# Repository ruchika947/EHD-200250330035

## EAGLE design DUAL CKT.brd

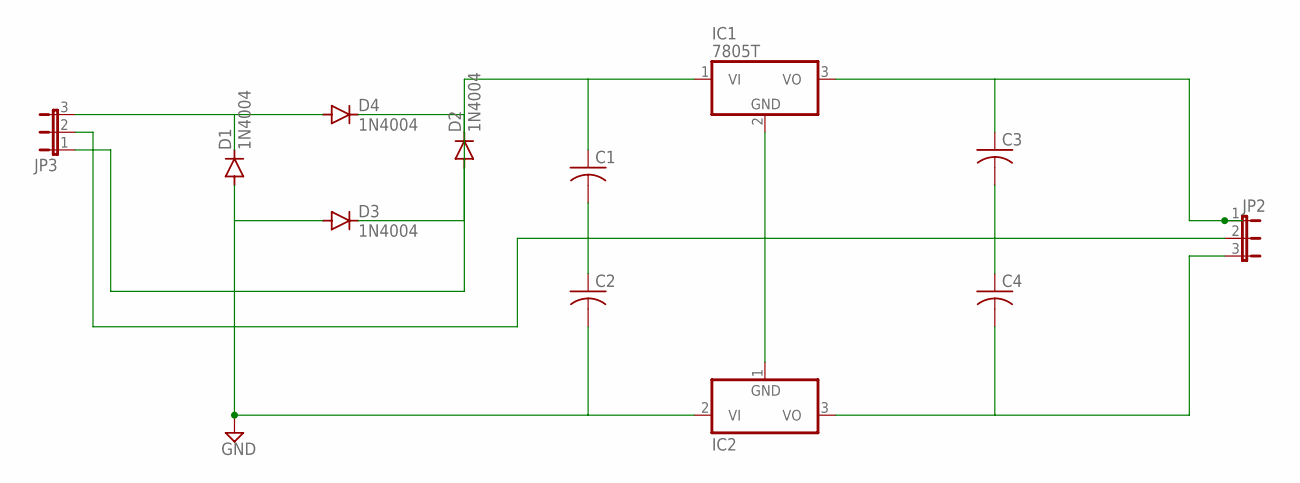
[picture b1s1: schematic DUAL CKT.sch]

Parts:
C1, C2, C3, C4: C-US025-024X044; C025-024X044
D1, D2, D3, D4: 1N4004; DO41-10
IC1: 7805T; TO220H
IC2: 7905T; TO220H
JP2, JP3: JP2W

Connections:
GND: C2.2, D1.A, D3.A, IC2.2 (VI)
unnamed: D1.C, D4.A, JP3.3
unnamed: C1.1, D2.C, D4.C, IC1.1 (VI), JP3.1
unnamed: JP2.2, JP3.2
unnamed: C1.2, C2.1
unnamed: C3.1, IC1.3 (VO), JP2.1
unnamed: C4.2, IC2.3 (VO), JP2.3
unnamed: IC1.2 (GND), IC2.1 (GND)
unnamed: C3.2, C4.1
unnamed: D2.A, D3.C

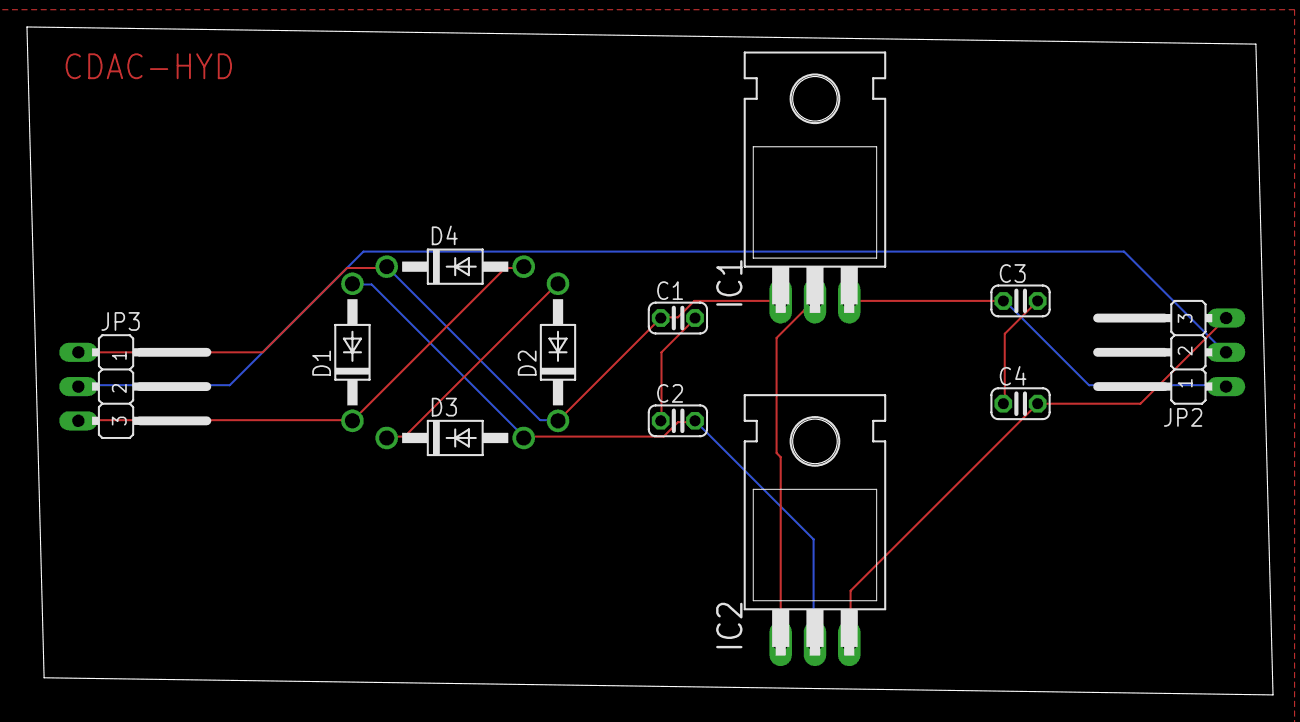
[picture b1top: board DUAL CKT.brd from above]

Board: 2 copper layers, 92.4 x 49.5 mm, 12 parts (0 on the bottom side), 10 nets.

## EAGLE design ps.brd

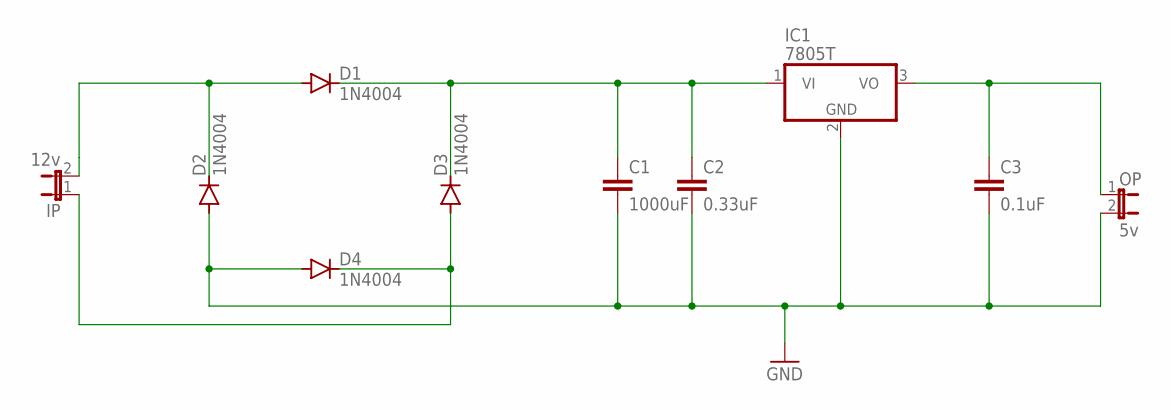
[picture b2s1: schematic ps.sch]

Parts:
C1: 1000uF; C2.5-3
C2: 0.33uF; C2.5-3
C3: 0.1uF; C2.5-3
D1, D2, D3, D4: 1N4004; DO41-10
IC1: 7805T; TO220H
IP: 12v; JP1
OP: 5v; JP1

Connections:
GND: C1.2, C2.2, C3.2, D2.A, D4.A, IC1.2 (GND), OP.2
unnamed: D1.A, D2.C, IP.2
unnamed: C1.1, C2.1, D1.C, D3.C, IC1.1 (VI)
unnamed: D3.A, D4.C, IP.1
unnamed: C3.1, IC1.3 (VO), OP.1

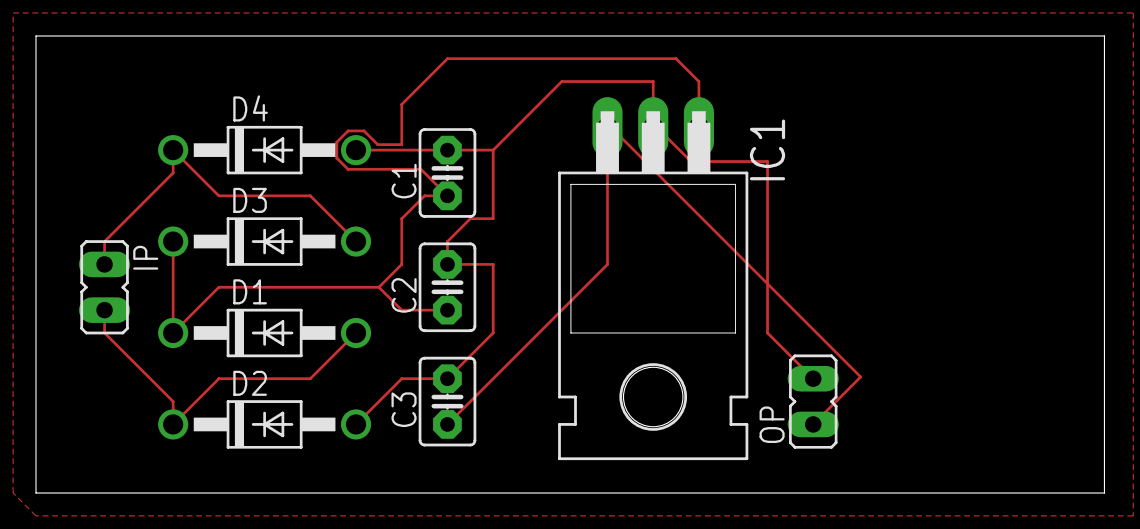
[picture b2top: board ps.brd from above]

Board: 2 copper layers, 59.4 x 25.4 mm, 10 parts (0 on the bottom side), 5 nets.

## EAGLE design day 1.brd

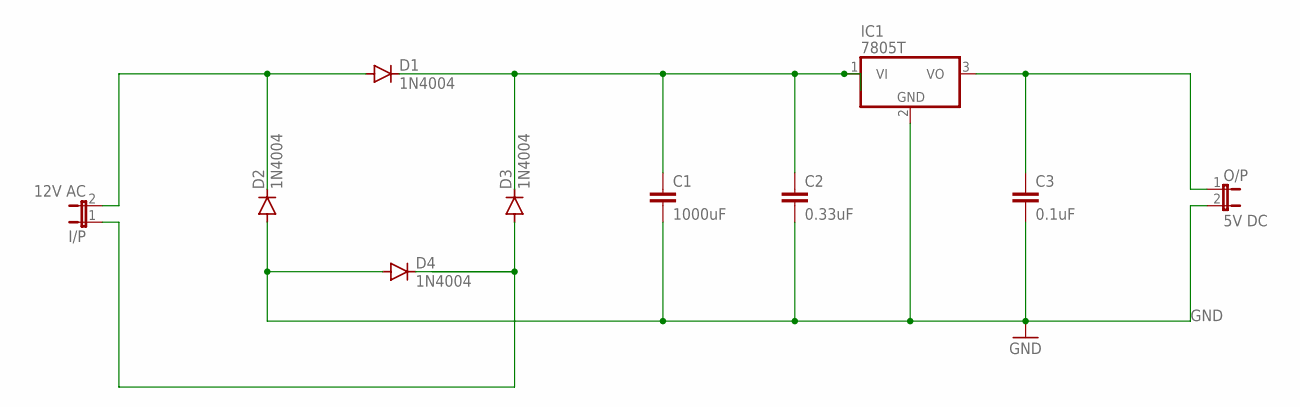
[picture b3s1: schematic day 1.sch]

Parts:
C1: 1000uF; C2.5-3
C2: 0.33uF; C2.5-3
C3: 0.1uF; C2.5-3
D1, D2, D3, D4: 1N4004; DO41-10
I/P: 12V AC; JP1
IC1: 7805T; TO220H
O/P: 5V DC; JP1

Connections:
GND: C1.2, C2.2, C3.2, D2.A, D4.A, IC1.2 (GND), O/P.2
unnamed: C3.1, IC1.3 (VO), O/P.1
unnamed: D3.A, D4.C, I/P.1
unnamed: D1.A, D2.C, I/P.2
unnamed: C1.1, C2.1, D1.C, D3.C, IC1.1 (VI)

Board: 2 copper layers, 10 parts (0 on the bottom side), 5 nets, no tracks yet.
